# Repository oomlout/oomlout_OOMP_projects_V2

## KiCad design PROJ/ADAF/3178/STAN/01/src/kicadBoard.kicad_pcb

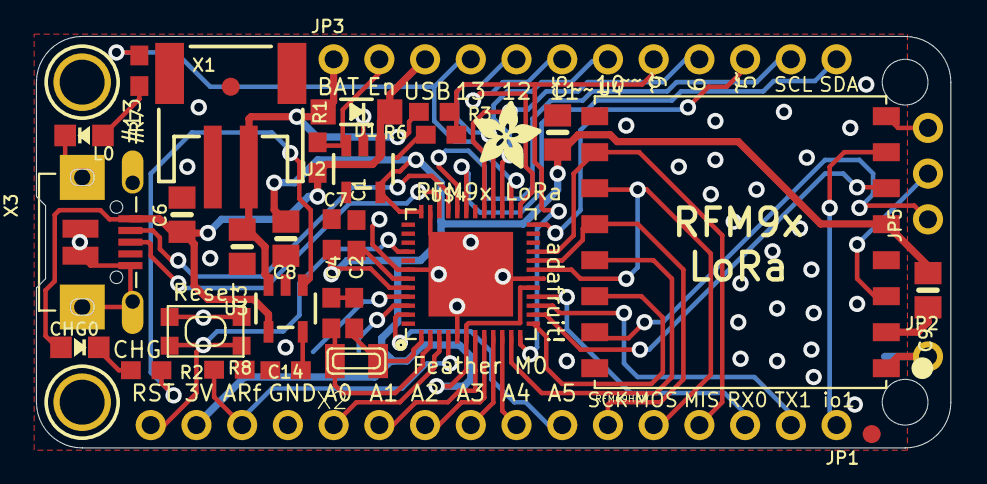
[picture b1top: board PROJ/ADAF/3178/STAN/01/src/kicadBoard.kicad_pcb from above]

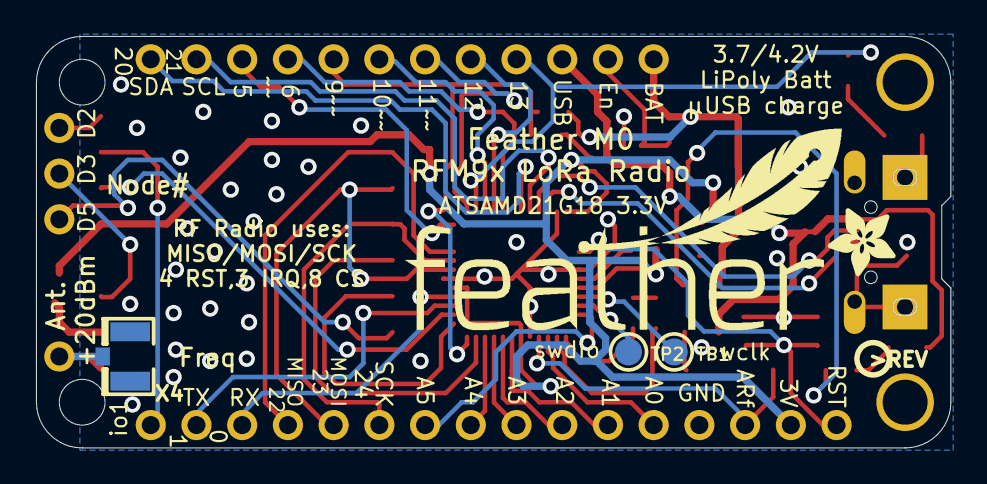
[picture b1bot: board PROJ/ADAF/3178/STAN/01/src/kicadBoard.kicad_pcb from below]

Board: 2 copper layers, 50.8 x 22.9 mm, 44 parts (6 on the bottom side), 46 nets.

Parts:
@HOLE0, @HOLE1: (no value)
C1, C7, C14: 1uF; 0603-NO
C2, C4: 22pF; 0603-NO
C3, C6, C8: 10µF; 0805-NO
C5, C9: 10uF; 0805-NO
CHG0: ORANGE; CHIPLED_0805_NOOUTLINE
D1: MBR120; SOD-123
JP1: 1X16_ROUND
JP2: 1X01_ROUND
JP3: 1X12_ROUND
JP5: 1X03_ROUND
L0: RED; CHIPLED_0805_NOOUTLINE
R1, R3: 100k; 0603-NO
R2: 1K; 0603-NO
R6: 100K; 0603-NO
R7: 2.2K; 0603-NO
R8: 10K\; 0603-NO
SW1: SPST_TACT-KMR2; KMR2
TP1, TP2: TESTPOINT_ROUND_1.5MM
U2: AP2112K-3.3; SOT23-5
U3: MCP73831T-2ACI/OT; SOT23-5
U4: RFM69HCW; RFMHCW_SMT
U$4: ATSAMD21G18_QFN; TQFN48_7MM
U$7, U$12: ADAFRUIT_3.5MM
U$9: FEATHERLOGO
U$13: PCBFEAT-REV-040
U$31, U$32: MOUNTINGHOLE2.5; MOUNTINGHOLE_2.5_PLATED
U$34, U$35: FIDUCIAL""; FIDUCIAL_1MM
X1: JSTPH; JSTPH2
X2: 32.768; XTAL3215
X3: microUSB; 4UCONN_20329_V2
X4: uFL; U.FL

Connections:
+3V3: C5.1, C7.1, C8.1, C9.1, JP1.15, U2.5, U4.5P, U$4.6, U$4.17, U$4.36, U$4.44
A0: JP1.12, U$4.3
A1: JP1.11, U$4.7
A2: JP1.10, U$4.8
A3: JP1.9, U$4.9
A4: JP1.8, U$4.10
A5: JP1.7, U$4.47
ANT: JP2.1, U4.1P, X4.3
AREF: C14.1, JP1.14, U$4.4
D0: JP1.3, U$4.16
D1: JP1.2, U$4.15
D3_IRQ: U4.6P, U$4.14
D4_RST: U4.14P, U$4.13
D5: JP3.10, U$4.24
D6: JP3.9, U$4.29
D8_CS: U4.13P, U$4.11
D9: JP3.8, R3.2, R6.1, U$4.12
D10: JP3.7, U$4.27
D11: JP3.6, U$4.25
D12: JP3.5, U$4.28
D13: JP3.4, R7.1, U$4.26
D+: U$4.34, X3.D+
D-: U$4.33, X3.D-
DIO1: JP1.1, U4.7P
DIO2: JP5.3, U4.8P
DIO3: JP5.2, U4.3P
DIO5: JP5.1, U4.15P
EN: JP3.2, R1.2, U2.3
GND: C1.2, C2.2, C3.2, C4.2, C5.2, C6.2, C7.2, C8.2, C9.2, C14.2, JP1.13, L0.C, R6.2, R8.2, SW1.2, SW1.4, U2.2, U3.2, U4.2P, U4.9P, U4.16P, U$4.5, U$4.18, U$4.35, U$4.42, U$4.THERMAL, X1.1, X3.BASE@1, X3.BASE@2, X3.GND, X3.SPRT@1, X3.SPRT@2, X3.SPRT@3, X3.SPRT@4, X4.1, X4.2
MISO: JP1.4, U4.10P, U$4.21
MOSI: JP1.5, U4.11P, U$4.19
unnamed: CHG0.C, R2.1
unnamed: L0.A, R7.2
unnamed: R2.2, U3.1
unnamed: R8.1, U3.5
unnamed: C2.1, U$4.1, X2.P$1
unnamed: C4.1, U$4.2, X2.P$2
SCK: JP1.6, U4.12P, U$4.20
SCL: JP3.11, U$4.32
SDA: JP3.12, U$4.31
SWCLK: TP1.P$1, U$4.45
SWDIO: TP2.P$1, U$4.46
VBAT: C3.1, D1.A, JP3.1, R3.1, U3.3, X1.2
VBUS: C6.1, CHG0.A, D1.C, JP3.3, R1.1, U2.1, U3.4, X3.VBUS
VDDCORE: C1.1, U$4.43
~RESET: JP1.16, SW1.1, SW1.3, U$4.40

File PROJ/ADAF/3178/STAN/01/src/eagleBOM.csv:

"Part";"Value";"Device";"Package";"Description";"BOM";
"C1";"1uF";"CAP_CERAMIC0603_NO";"0603-NO";"Ceramic Capacitors";"";
"C2";"22pF";"CAP_CERAMIC0603_NO";"0603-NO";"Ceramic Capacitors";"";
"C3";"10µF";"CAP_CERAMIC0805-NOOUTLINE";"0805-NO";"Ceramic Capacitors";"";
"C4";"22pF";"CAP_CERAMIC0603_NO";"0603-NO";"Ceramic Capacitors";"";
"C5";"10uF";"CAP_CERAMIC0805-NOOUTLINE";"0805-NO";"Ceramic Capacitors";"";
"C6";"10µF";"CAP_CERAMIC0805-NOOUTLINE";"0805-NO";"Ceramic Capacitors";"";
"C7";"1uF";"CAP_CERAMIC0603_NO";"0603-NO";"Ceramic Capacitors";"";
"C8";"10µF";"CAP_CERAMIC0805-NOOUTLINE";"0805-NO";"Ceramic Capacitors";"";
"C9";"10uF";"CAP_CERAMIC0805-NOOUTLINE";"0805-NO";"Ceramic Capacitors";"";
"C14";"1uF";"CAP_CERAMIC0603_NO";"0603-NO";"Ceramic Capacitors";"";
"CHG";"ORANGE";"LED0805_NOOUTLINE";"CHIPLED_0805_NOOUTLINE";"LED";"";
"D1";"MBR120";"DIODE-SCHOTTKYSOD-123";"SOD-123";"";"";
"JP1";"";"HEADER-1X16ROUND";"1X16_ROUND";"PIN HEADER";"";
"JP2";"";"HEADER-1X1ROUND";"1X01_ROUND";"PIN HEADER";"";
"JP3";"";"HEADER-1X12";"1X12_ROUND";"";"";
"JP5";"";"HEADER-1X3ROUND";"1X03_ROUND";"PIN HEADER";"";
"L";"RED";"LED0805_NOOUTLINE";"CHIPLED_0805_NOOUTLINE";"LED";"";
"R1";"100k";"RESISTOR_0603_NOOUT";"0603-NO";"Resistors";"";
"R2";"1K";"RESISTOR_0603_NOOUT";"0603-NO";"Resistors";"";
"R3";"100k";"RESISTOR_0603_NOOUT";"0603-NO";"Resistors";"";
"R6";"100K";"RESISTOR_0603_NOOUT";"0603-NO";"Resistors";"";
"R7";"2.2K";"RESISTOR_0603_NOOUT";"0603-NO";"Resistors";"";
"R8";"10K\";"RESISTOR_0603_NOOUT";"0603-NO";"Resistors";"";
"SW1";"SPST_TACT-KMR2";"SPST_TACT-KMR2";"KMR2";"SMT 6mm switch, EVQQ2 series";"";
"TP1";"";"TESTPOINTROUND1.5MM";"TESTPOINT_ROUND_1.5MM";"Test Point";"";
"TP2";"";"TESTPOINTROUND1.5MM";"TESTPOINT_ROUND_1.5MM";"Test Point";"";
"U$4";"ATSAMD21G18_QFN";"ATSAMD21J_QFN";"TQFN48_7MM";"";"";
"U$31";"MOUNTINGHOLE2.5";"MOUNTINGHOLE2.5";"MOUNTINGHOLE_2.5_PLATED";"Mounting Hole";"EXCLUDE";
"U$32";"MOUNTINGHOLE2.5";"MOUNTINGHOLE2.5";"MOUNTINGHOLE_2.5_PLATED";"Mounting Hole";"EXCLUDE";
"U$34";"FIDUCIAL""";"FIDUCIAL""";"FIDUCIAL_1MM";"Fiducial Alignment Points";"EXCLUDE";
"U$35";"FIDUCIAL""";"FIDUCIAL""";"FIDUCIAL_1MM";"Fiducial Alignment Points";"EXCLUDE";
"U2";"AP2112K-3.3";"VREG_SOT23-5";"SOT23-5";"SOT23-5 Fixed Voltage Regulators";"";
"U3";"MCP73831T-2ACI/OT";"MCP73831/2";"SOT23-5";"MCP73831/2 LIPO Charger";"";
"U4";"RFM69HCW";"RFM69HCW_SMT";"RFMHCW_SMT";"RFM69HCW - ISM Band RF Transceiver";"";
"X1";"JSTPH";"CON_JST_PH_2PIN";"JSTPH2";"JST 2-Pin Right-Angle Connector";"";
"X2";"32.768";"XTAL-3.2X1.5";"XTAL3215";"Low cost SMT crystals, no capacitors included";"";
"X3";"microUSB";"USB_MICRO_20329_V2";"4UCONN_20329_V2";"USB Connectors";"";
"X4";"uFL";"ANTENNA_U.FL";"U.FL";"U.FL Antenna Connector";"";

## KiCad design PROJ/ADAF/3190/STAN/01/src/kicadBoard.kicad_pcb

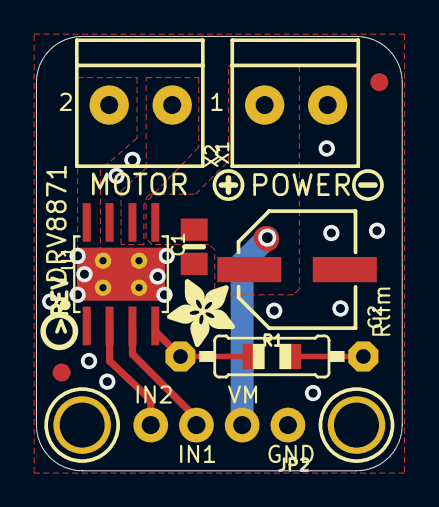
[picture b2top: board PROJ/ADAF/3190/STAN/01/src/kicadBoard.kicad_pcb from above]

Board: 2 copper layers, 20.3 x 24.1 mm, 15 parts (0 on the bottom side), 7 nets.

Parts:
C1: 0.1uF/50V; 0805-NO
C2: 22uF/63V; PANASONIC_D
FID1, FID2: FIDUCIAL""; FIDUCIAL_1MM
JP2: 1X04_ROUND_76
R1: 30K; 0805-THM
U1: DRV8871; HSOP8
U$9, U$10: MOUNTINGHOLE2.5; MOUNTINGHOLE_2.5_PLATED
U$11: SYMBOL_PLUS
U$12: SYMBOL_MINUS
U$14: ADAFRUIT_3.5MM
U$15: PCBFEAT-REV-040
X1: DCMOTOR; TERMBLOCK_1X2-3.5MM
X2: POWER; TERMBLOCK_1X2-3.5MM

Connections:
GND: C1.2, C2.-, JP2.1, R1.1, U1.1, U1.7, U1.GND, U1.P$1, U1.P$2, U1.P$3, U1.P$4, X2.2
IN1: JP2.3, U1.3
IN2: JP2.4, U1.2
unnamed: R1.2, U1.4
OUT1: U1.6, X1.2
OUT2: U1.8, X1.1
VMOTOR: C1.1, C2.+, JP2.2, U1.5, X2.1

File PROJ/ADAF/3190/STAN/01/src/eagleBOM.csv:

"Part";"Value";"Device";"Package";"Description";"BOM";
"C1";"0.1uF/50V";"CAP_CERAMIC0805-NOOUTLINE";"0805-NO";"Ceramic Capacitors";"";
"C2";"22uF/63V";"CAP_ELECTROLYTICPANASONIC_D";"PANASONIC_D";"Electrolytic Capacitors";"";
"FID1";"FIDUCIAL""";"FIDUCIAL""";"FIDUCIAL_1MM";"Fiducial Alignment Points";"EXCLUDE";
"FID2";"FIDUCIAL""";"FIDUCIAL""";"FIDUCIAL_1MM";"Fiducial Alignment Points";"EXCLUDE";
"JP2";"";"HEADER-1X476MIL";"1X04_ROUND_76";"PIN HEADER";"";
"R1";"30K";"FLIPFLOP-RES";"0805-THM";"Flip Flop resistor";"";
"U$9";"MOUNTINGHOLE2.5";"MOUNTINGHOLE2.5";"MOUNTINGHOLE_2.5_PLATED";"Mounting Hole";"EXCLUDE";
"U$10";"MOUNTINGHOLE2.5";"MOUNTINGHOLE2.5";"MOUNTINGHOLE_2.5_PLATED";"Mounting Hole";"EXCLUDE";
"U1";"DRV8871";"DRV8871";"HSOP8";"DRV8871 - 3.6A PWM Motor Driver";"";
"X1";"DCMOTOR";"TERMBLOCK_1X2";"TERMBLOCK_1X2-3.5MM";"3.5mm Terminal block";"";
"X2";"POWER";"TERMBLOCK_1X2";"TERMBLOCK_1X2-3.5MM";"3.5mm Terminal block";"";

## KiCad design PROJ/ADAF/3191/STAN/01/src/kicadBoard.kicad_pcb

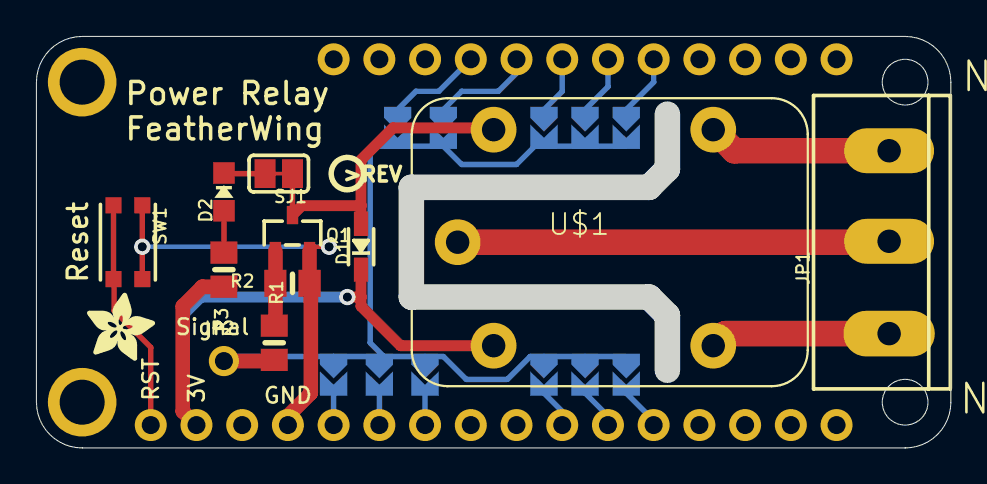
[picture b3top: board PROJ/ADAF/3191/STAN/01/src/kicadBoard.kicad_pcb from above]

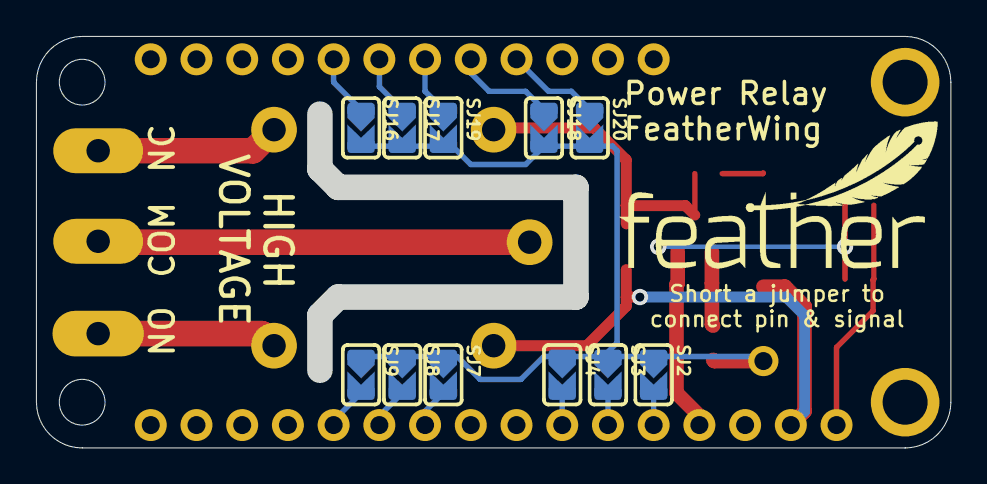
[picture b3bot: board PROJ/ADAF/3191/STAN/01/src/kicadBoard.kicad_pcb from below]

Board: 2 copper layers, 50.8 x 22.9 mm, 26 parts (12 on the bottom side), 22 nets.

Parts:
D1: 1N4148; SOD-323
D2: RED; CHIPLED_0805_NOOUTLINE
JP1: TERMBLOCK_1X3_5.08MM
JP2: 1X01_ROUND
MS2: FEATHERWING
Q1: MMBT2222; SOT23-R
R1, R3: 1K; 0805-NO
R2: 10K; 0805-NO
SJ1: SOLDERJUMPER_CLOSEDWIRE
SJ2, SJ3, SJ4, SJ7, SJ8, SJ9, SJ16, SJ17, SJ18, SJ19, SJ20: SOLDERJUMPER_ARROW_NOPASTE
SW1: KMR2; BTN_KMR2_4.6X2.8
U$1: RELAY_G5LE; RELAY_G5LE-1
U$5: PCBFEAT-REV-040
U$6: ADAFRUIT_3.5MM
U$7: FEATHERLOGO_MED

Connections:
3.3V: D1.C, MS2.2, R3.2, U$1.2
GND: MS2.4, Q1.2, R2.1, SW1.A, SW1.A'
unnamed: JP1.2, U$1.1
unnamed: JP1.3, U$1.3
unnamed: JP1.1, U$1.4
unnamed: D1.A, Q1.3, SJ1.1, U$1.5
unnamed: MS2.12, SJ9.2
unnamed: MS2.11, SJ8.2
unnamed: MS2.10, SJ7.2
unnamed: MS2.7, SJ4.2
unnamed: MS2.6, SJ3.2
unnamed: MS2.5, SJ2.2
unnamed: MS2.25, SJ20.1
unnamed: MS2.24, SJ18.1
unnamed: MS2.1, SW1.B, SW1.B'
unnamed: MS2.23, SJ19.1
unnamed: MS2.22, SJ17.1
unnamed: MS2.21, SJ16.1
unnamed: Q1.1, R1.2, R2.2
unnamed: D2.C, SJ1.2
unnamed: D2.A, R3.1
RELAYSIGNAL: JP2.1, R1.1, SJ2.1, SJ3.1, SJ4.1, SJ7.1, SJ8.1, SJ9.1, SJ16.2, SJ17.2, SJ18.2, SJ19.2, SJ20.2

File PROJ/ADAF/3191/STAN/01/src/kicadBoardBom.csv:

"Id";"Designator";"Package";"Quantity";"Designation";"Supplier and ref";
1;"Q1";"SOT23-R";1;"MMBT2222";;;
2;"R1,R3";"0805-NO";2;"1K";;;
3;"D1";"SOD-323";1;"1N4148";;;
4;"U$6";"ADAFRUIT_3.5MM";1;"";;;
5;"MS2";"FEATHERWING";1;"FEATHERWING";;;
6;"U$5";"PCBFEAT-REV-040";1;"";;;
7;"JP1";"TERMBLOCK_1X3_5.08MM";1;"";;;
8;"U$1";"RELAY_G5LE-1";1;"RELAY_G5LE";;;
9;"R2";"0805-NO";1;"10K";;;
10;"D2";"CHIPLED_0805_NOOUTLINE";1;"RED";;;
11;"SJ1";"SOLDERJUMPER_CLOSEDWIRE";1;"";;;
12;"SW1";"BTN_KMR2_4.6X2.8";1;"KMR2";;;
13;"JP2";"1X01_ROUND";1;"";;;
14;"U$7";"FEATHERLOGO_MED";1;"";;;
15;"SJ20,SJ8,SJ9,SJ4,SJ18,SJ17,SJ2,SJ3,SJ16,SJ19,SJ7";"SOLDERJUMPER_ARROW_NOPASTE";11;"";;;

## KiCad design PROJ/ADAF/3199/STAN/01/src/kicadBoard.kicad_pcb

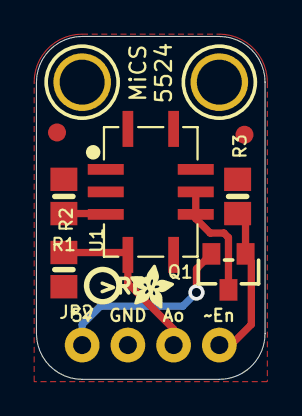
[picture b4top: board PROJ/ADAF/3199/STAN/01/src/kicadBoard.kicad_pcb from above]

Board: 2 copper layers, 12.7 x 19.0 mm, 12 parts (0 on the bottom side), 6 nets.

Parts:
FID1, FID2: FIDUCIAL""; FIDUCIAL_1MM
JP2: 1X04_ROUND_76
Q1: DMG3415U; SOT23-WIDE
R1: 82Ω 1%; 0805-NO
R2, R3: 10K; 0805-NO
U1: MiCS-5524; MICS-5524
U$3, U$4: MOUNTINGHOLE2.5; MOUNTINGHOLE_2.5_PLATED
U$7: ADAFRUIT_2.5MM
U$10: PCBFEAT-REV-040

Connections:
5.0V: JP2.1, Q1.2
AOUT: JP2.3, R2.2, U1.D
ENABLE: JP2.4, Q1.1, R3.1
GND: JP2.2, R1.1, R2.1, R3.2
HEATER: R1.2, U1.C
unnamed: Q1.3, U1.F, U1.G

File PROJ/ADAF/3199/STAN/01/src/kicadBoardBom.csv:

"Id";"Designator";"Package";"Quantity";"Designation";"Supplier and ref";
1;"U$4,U$3";"MOUNTINGHOLE_2.5_PLATED";2;"MOUNTINGHOLE2.5";;;
2;"U$7";"ADAFRUIT_2.5MM";1;"";;;
3;"JP2";"1X04_ROUND_76";1;"";;;
4;"R1";"0805-NO";1;"82Ω 1%";;;
5;"FID2,FID1";"FIDUCIAL_1MM";2;"FIDUCIAL""";;;
6;"Q1";"SOT23-WIDE";1;"DMG3415U";;;
7;"R2,R3";"0805-NO";2;"10K";;;
8;"U1";"MICS-5524";1;"MiCS-5524";;;
9;"U$10";"PCBFEAT-REV-040";1;"";;;

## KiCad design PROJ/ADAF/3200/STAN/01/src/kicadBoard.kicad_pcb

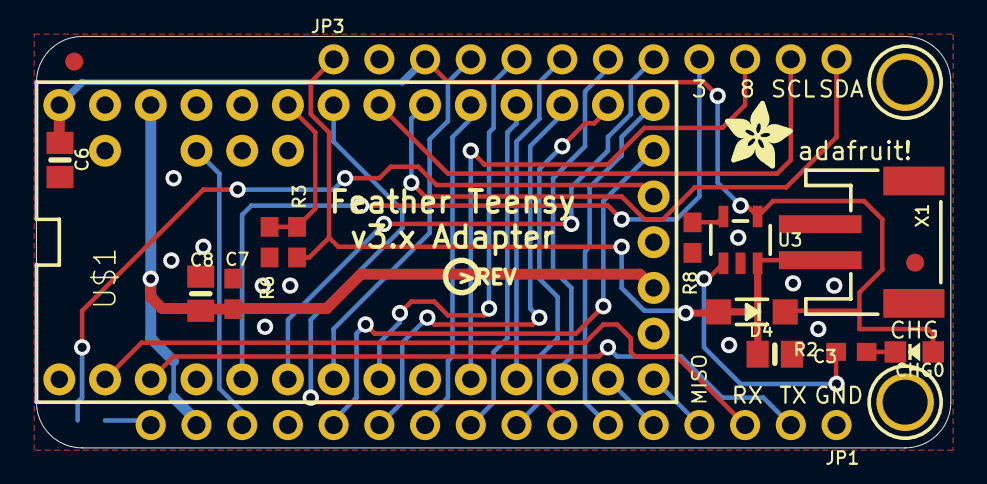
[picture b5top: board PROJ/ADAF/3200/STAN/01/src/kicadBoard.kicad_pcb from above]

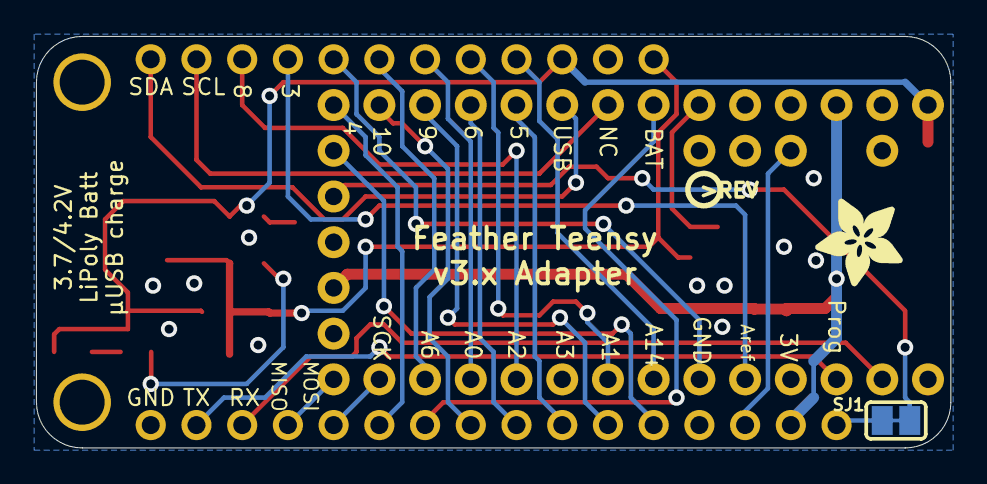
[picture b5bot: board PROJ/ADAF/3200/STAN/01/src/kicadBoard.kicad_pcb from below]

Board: 2 copper layers, 50.8 x 22.9 mm, 24 parts (3 on the bottom side), 31 nets.

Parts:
C3, C6, C8: 10µF; 0805-NO
C7: 1uF; 0603-NO
CHG0: ORANGE; CHIPLED_0805_NOOUTLINE
D4: MBR120; SOD-123
JP1: 1X16_ROUND
JP3: 1X12_ROUND
R2: 1K; 0603-NO
R3: 100k; 0603-NO
R6: 100K; 0603-NO
R8: 2.2K; 0603-NO
SJ1: SOLDERJUMPER_CLOSEDWIRE
U3: MCP73831T-2ACI/OT; SOT23-5
U$1: TEENSY_3.1_ALL_PINS; TEENSY3-ALL_PINS
U$4: ADAFRUIT_5MM
U$5, U$6: PCBFEAT-REV-040
U$7: ADAFRUIT_3.5MM
U$31, U$32: MOUNTINGHOLE2.5; MOUNTINGHOLE_2.5_PLATED
U$34, U$35: FIDUCIAL""; FIDUCIAL_1MM
X1: JSTPH; JSTPH2

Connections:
3: JP3.9, U$1.3
4: JP3.8, U$1.4
5: JP3.4, U$1.5
6: JP3.5, U$1.6
8: JP3.10, U$1.8
9: JP3.6, U$1.9
10: JP3.7, U$1.10
+3V3: C7.1, C8.1, JP1.15, U$1.3.3V, U$1.3.3V1
A0: JP1.8, U$1.14/A0
A1: JP1.11, U$1.15/A1
A2: JP1.9, U$1.16/A2
A3: JP1.10, U$1.17/A3
A6: JP1.7, U$1.20/A6
A7: R3.2, R6.1, U$1.21/A7
A14: JP1.12, U$1.RESET/DAC
AREF: JP1.14, U$1.AREF
BOOT: SJ1.2, U$1.PGM
GND: C3.2, C6.2, C7.2, C8.2, JP1.1, JP1.13, R6.2, R8.2, U3.2, U$1.GND, U$1.GND1, X1.1
MISO: JP1.4, U$1.12
MOSI: JP1.5, U$1.11
unnamed: CHG0.C, R2.1
unnamed: R2.2, U3.1
unnamed: R8.1, U3.5
RST/BOOT: JP1.16, SJ1.1
RX: JP1.3, U$1.0
SCK: JP1.6, U$1.13
SCL: JP3.11, U$1.19/A5
SDA: JP3.12, U$1.18/A4
TX: JP1.2, U$1.1
VBAT: C3.1, D4.A, JP3.1, R3.1, U3.3, X1.2
VBUS: C6.1, CHG0.A, D4.C, JP3.3, U3.4, U$1.VIN

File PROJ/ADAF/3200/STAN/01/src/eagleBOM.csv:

"Part";"Value";"Device";"Package";"Description";"BOM";
"C3";"10µF";"CAP_CERAMIC0805-NOOUTLINE";"0805-NO";"Ceramic Capacitors";"";
"C6";"10µF";"CAP_CERAMIC0805-NOOUTLINE";"0805-NO";"Ceramic Capacitors";"";
"C7";"1uF";"CAP_CERAMIC0603_NO";"0603-NO";"Ceramic Capacitors";"";
"C8";"10µF";"CAP_CERAMIC0805-NOOUTLINE";"0805-NO";"Ceramic Capacitors";"";
"CHG";"ORANGE";"LED0805_NOOUTLINE";"CHIPLED_0805_NOOUTLINE";"LED";"";
"D4";"MBR120";"DIODE-SCHOTTKYSOD-123";"SOD-123";"";"";
"JP1";"";"HEADER-1X16ROUND";"1X16_ROUND";"PIN HEADER";"";
"JP3";"";"HEADER-1X12";"1X12_ROUND";"";"";
"R2";"1K";"RESISTOR_0603_NOOUT";"0603-NO";"Resistors";"";
"R3";"100k";"RESISTOR_0603_NOOUT";"0603-NO";"Resistors";"";
"R6";"100K";"RESISTOR_0603_NOOUT";"0603-NO";"Resistors";"";
"R8";"2.2K";"RESISTOR_0603_NOOUT";"0603-NO";"Resistors";"";
"SJ1";"";"SOLDERJUMPERCLOSED";"SOLDERJUMPER_CLOSEDWIRE";"SMD Solder JUMPER";"";
"U$1";"TEENSY_3.1_ALL_PINS";"TEENSY_3.1_ALL_PINS";"TEENSY3-ALL_PINS";"Footprint for Teensy 3.1 or 3.2 board using all through-holes, i.e. the entire perimeter plus the 4 through-holes inboard (A10,A11,AREF, VUSB)";"";
"U$31";"MOUNTINGHOLE2.5";"MOUNTINGHOLE2.5";"MOUNTINGHOLE_2.5_PLATED";"Mounting Hole";"EXCLUDE";
"U$32";"MOUNTINGHOLE2.5";"MOUNTINGHOLE2.5";"MOUNTINGHOLE_2.5_PLATED";"Mounting Hole";"EXCLUDE";
"U$34";"FIDUCIAL""";"FIDUCIAL""";"FIDUCIAL_1MM";"Fiducial Alignment Points";"EXCLUDE";
"U$35";"FIDUCIAL""";"FIDUCIAL""";"FIDUCIAL_1MM";"Fiducial Alignment Points";"EXCLUDE";
"U3";"MCP73831T-2ACI/OT";"MCP73831/2";"SOT23-5";"MCP73831/2 LIPO Charger";"";
"X1";"JSTPH";"CON_JST_PH_2PIN";"JSTPH2";"JST 2-Pin Right-Angle Connector";"";

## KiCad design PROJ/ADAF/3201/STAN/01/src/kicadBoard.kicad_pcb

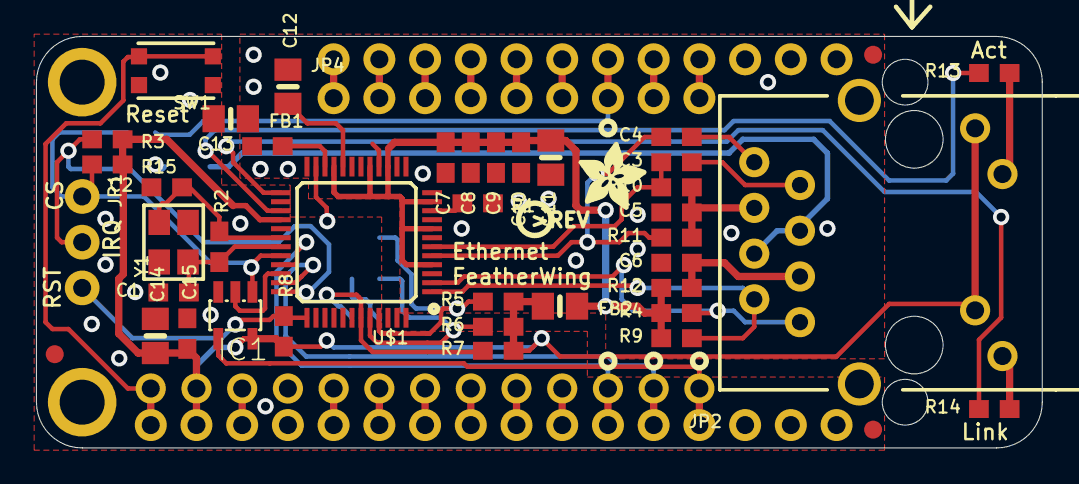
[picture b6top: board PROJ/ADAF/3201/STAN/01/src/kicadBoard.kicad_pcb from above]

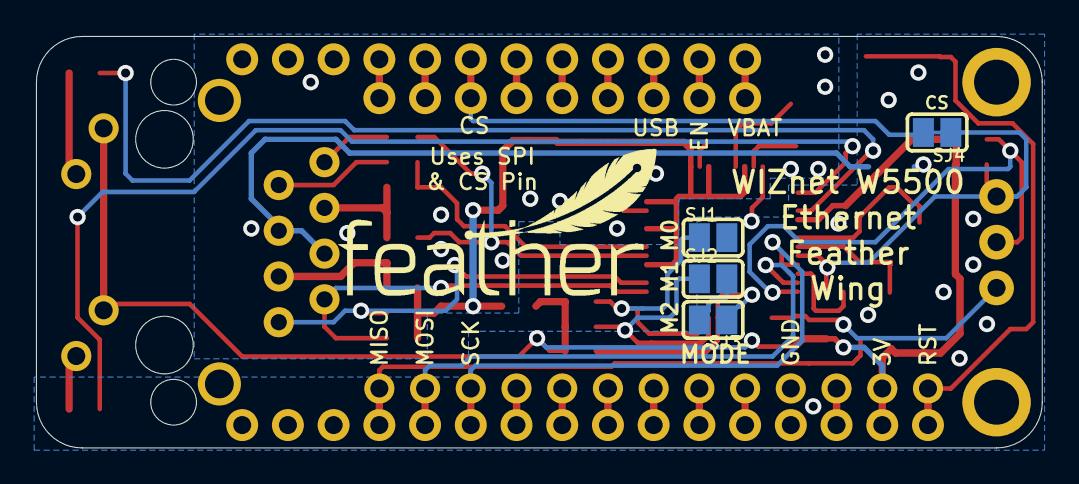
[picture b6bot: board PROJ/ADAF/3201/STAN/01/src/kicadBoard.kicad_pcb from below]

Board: 2 copper layers, 55.9 x 22.9 mm, 51 parts (5 on the bottom side), 48 nets.

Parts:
C1, C2: 22pF; 0603-NO
C3, C4: 6.8nF; 0603-NO
C5, C6: 10nF; 0603-NO
C7, C8, C9, C10, C13, C15: 0.1uF; 0603-NO
C11, C12, C14: 10uF; 0805-NO
FB1, FB2: ferrite; 0805-NO
FID1, FID2, FID3: FIDUCIAL""; FIDUCIAL_1MM
IC1: 74AHC1G125; SOT23-5L
JP1: 1X03_ROUND_76
JP2: 1X13_ROUND_70
JP4: 1X09_ROUND_70
MS1: FEATHERWING_NODIM
R1: 12.4K; 0603-NO
R2: 1M; 0603-NO
R3, R5, R6, R7, R8, R15: 10K; 0603-NO
R4, R9, R10, R11: 49.9; 0603-NO
R12: 10; 0603-NO
R13, R14: 470; 0603-NO
SJ1, SJ2, SJ3: SOLDERJUMPER_REFLOW_NOPASTE
SJ4: SOLDERJUMPER_CLOSEDWIRE
SW1: KMR2; BTN_KMR2_4.6X2.8
U$1: W5500; LQFP48
U$45: PCBFEAT-REV-040
U$48: FEATHERLOGO_MED
U$49: ADAFRUIT_3.5MM
X1: RB1-125BAG1A; RJ45_PULSEJACK
Y1: 25MHz; CRYSTAL_3.2X2.5

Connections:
3.3V: C14.1, C15.1, FB2.1, IC1.5, JP2.12, MS1.2, R3.2, R5.1, R6.1, R7.1, R8.1, R15.2, U$1.28, X1.10, X1.12
AGND: C5.2, C6.2, C7.2, C8.2, C9.2, C10.2, C11.2, C12.2, C13.2, FB1.2, R1.2, U$1.3, U$1.9, U$1.14, U$1.16, U$1.19, U$1.48
AVDD: C7.1, C8.1, C9.1, C10.1, C11.1, FB2.2, R4.2, R9.2, R12.2, U$1.4, U$1.8, U$1.11, U$1.15, U$1.17, U$1.21
CS: IC1.1, JP1.1, R15.1, SJ4.1, U$1.32
GND: C1.2, C2.2, C14.2, C15.2, FB1.1, IC1.3, JP2.10, MS1.4, SJ1.2, SJ2.2, SJ3.2, SW1.A, SW1.A', U$1.23, U$1.29, X1.4, X1.5
GREENLED: R14.1, X1.9
IRQ: JP1.2, R3.1, U$1.36
MISO: IC1.2, U$1.34
MISO_MCU: IC1.4, JP2.1, MS1.13
MOSI: JP2.2, MS1.12, U$1.35
unnamed: C1.1, R2.1, U$1.31, Y1.1
unnamed: C2.1, R2.2, U$1.30, Y1.2
unnamed: R1.1, U$1.10
unnamed: R5.2, SJ1.1, U$1.45
unnamed: R6.2, SJ2.1, U$1.44
unnamed: R7.2, SJ3.1, U$1.43
unnamed: C3.1, X1.7
unnamed: C4.1, X1.8
unnamed: C5.1, R10.1, R11.1, X1.6
unnamed: C6.1, R12.1, X1.3
unnamed: C13.1, U$1.22
unnamed: C12.1, U$1.20
unnamed: R13.2, U$1.27
unnamed: R14.2, U$1.25
unnamed: JP4.2, MS1.27
unnamed: JP4.4, MS1.25
unnamed: JP4.5, MS1.24
unnamed: JP4.6, MS1.23
unnamed: JP4.7, MS1.22, SJ4.2
unnamed: JP4.8, MS1.21
unnamed: JP4.9, MS1.20
unnamed: JP2.13, MS1.1, SW1.B, SW1.B'
unnamed: JP2.4, MS1.10
unnamed: JP2.5, MS1.9
unnamed: JP2.6, MS1.8
unnamed: JP2.7, MS1.7
unnamed: JP2.8, MS1.6
unnamed: JP2.9, MS1.5
unnamed: JP2.11, MS1.3
RESET: JP1.3, R8.2, U$1.37
RX+: C3.2, R10.2, U$1.6
RX-: C4.2, R11.2, U$1.5
SCK: JP2.3, MS1.11, U$1.33
TX+: R4.1, U$1.2, X1.1
TX-: R9.1, U$1.1, X1.2
USB: JP4.3, MS1.26
VBAT: JP4.1, MS1.28
YELLOWLED: R13.1, X1.11

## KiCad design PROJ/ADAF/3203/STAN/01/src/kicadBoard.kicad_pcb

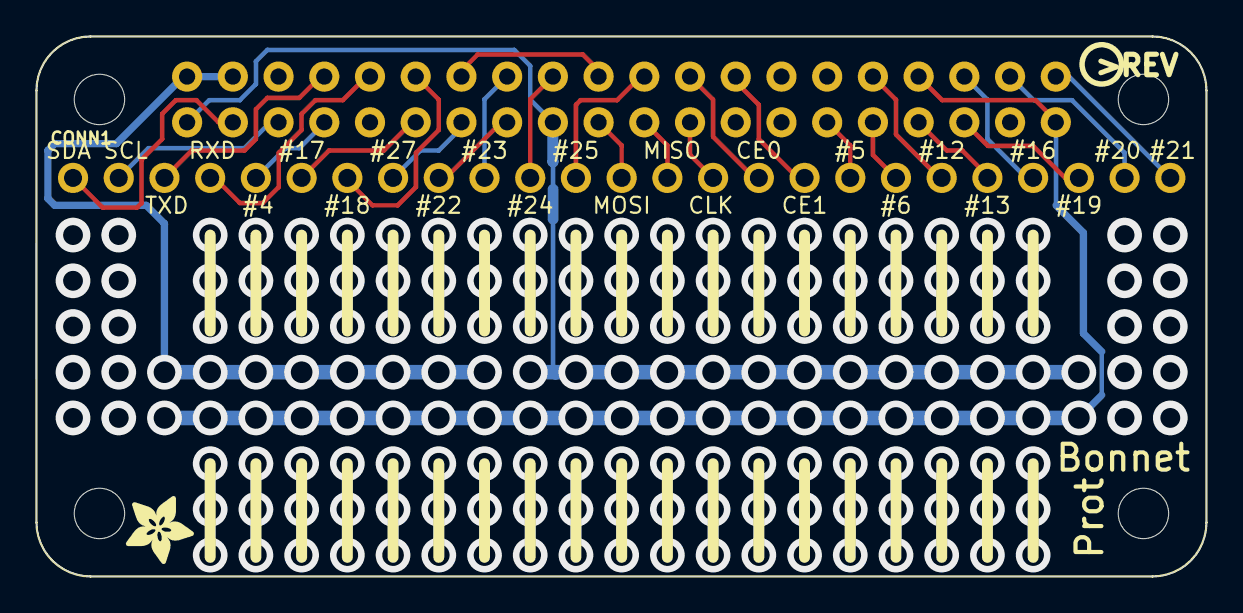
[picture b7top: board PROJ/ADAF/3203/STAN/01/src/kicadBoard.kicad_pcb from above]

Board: 2 copper layers, 65.0 x 30.0 mm, 4 parts (0 on the bottom side), 28 nets.

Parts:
CONN1: HEADER-1X25; 1X25_ROUND_70MIL
RPI1: RASPBERRYPI_BPLUS_BONNETNODIM; PI_BONNET_NODIM
U$1: ADAFRUIT_3.5MM
U$3: PCBFEAT-REV-056

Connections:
3.3V: RPI1.1, RPI1.17
5.0V: RPI1.2, RPI1.4
GND: RPI1.6, RPI1.9, RPI1.14, RPI1.20, RPI1.25, RPI1.30, RPI1.34, RPI1.39
GPIO4: CONN1.5, RPI1.7
GPIO5: CONN1.18, RPI1.29
GPIO6: CONN1.19, RPI1.31
GPIO12: CONN1.20, RPI1.32
GPIO13: CONN1.21, RPI1.33
GPIO16: CONN1.22, RPI1.36
GPIO17: CONN1.6, RPI1.11
GPIO18: CONN1.7, RPI1.12
GPIO19: CONN1.23, RPI1.35
GPIO20: CONN1.24, RPI1.38
GPIO21: CONN1.25, RPI1.40
GPIO22: CONN1.9, RPI1.15
GPIO23: CONN1.10, RPI1.16
GPIO24: CONN1.11, RPI1.18
GPIO25: CONN1.12, RPI1.22
GPIO27: CONN1.8, RPI1.13
RXD: CONN1.4, RPI1.10
SCL: CONN1.2, RPI1.5
SDA: CONN1.1, RPI1.3
SPI_CE0: CONN1.16, RPI1.24
SPI_CE1: CONN1.17, RPI1.26
SPI_MISO: CONN1.14, RPI1.21
SPI_MOSI: CONN1.13, RPI1.19
SPI_SCLK: CONN1.15, RPI1.23
TXD: CONN1.3, RPI1.8

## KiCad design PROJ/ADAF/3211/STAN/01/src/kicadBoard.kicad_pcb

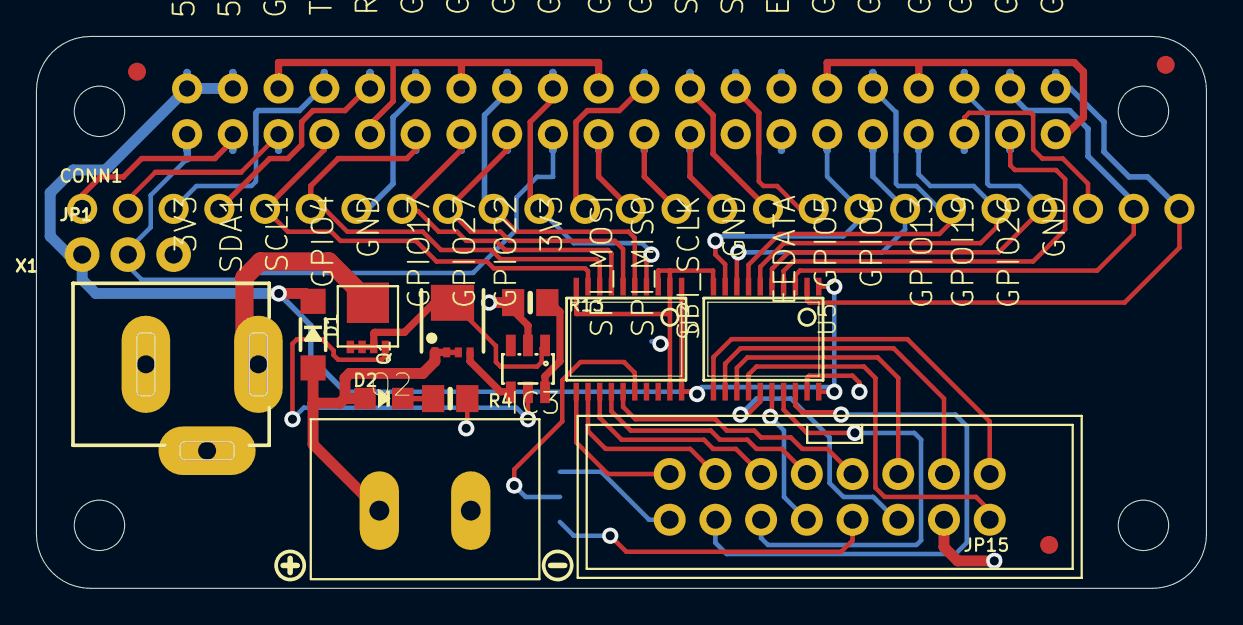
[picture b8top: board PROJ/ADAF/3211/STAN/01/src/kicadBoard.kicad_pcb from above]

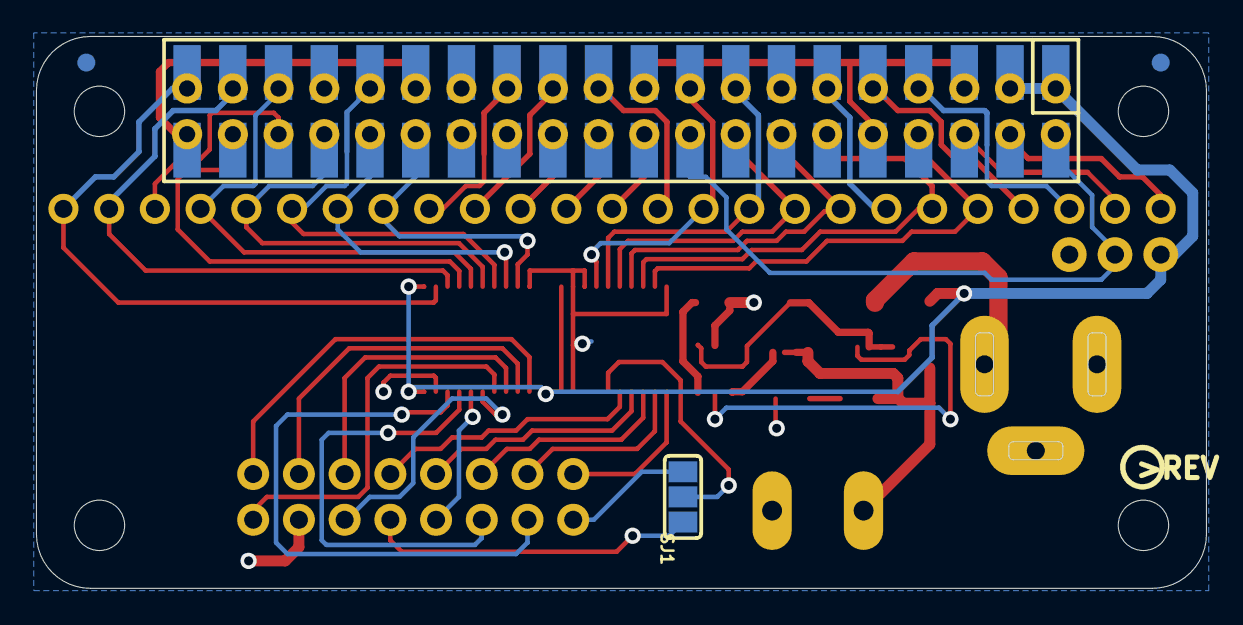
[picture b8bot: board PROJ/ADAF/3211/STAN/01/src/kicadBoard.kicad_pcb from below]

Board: 2 copper layers, 65.0 x 30.7 mm, 24 parts (3 on the bottom side), 54 nets.

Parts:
CONN1: HEADER-1X25; 1X25_ROUND_70MIL
D1: MBR120; SOD-123
D2: green; CHIPLED_0805_NOOUTLINE
FID1, FID2, FID3: FIDUCIAL_1MM
IC3: MAX4866T; SOT23-6
JP1: 1X03_ROUND_76
JP15: 2X08_SHROUDED
MATRIX_PWR0: PINHEAD; TERMBLOCK508
Q1: AON3414; POWERPAK-1212-8
Q2: AON7401; POWERDI3333
R4, R13: 1K; 0805-NO
RPI1: RASPBERRYPI_BPLUS_BONNET_THMSMT; PI_BONNET_THMSMT
SJ1: SOLDERJUMPER_2WAY_OPEN_NOPASTE
U3, U5: 74AHCT245; TSSOP20
U$1: BONNET_MATRIX_TOP
U$3: PCBFEAT-REV-056
U$6: BONNET_MATRIX_BOT
U$10: SYMBOL_PLUS
U$11: SYMBOL_MINUS
X1: 2.1mm DC; DCJACK_2MM_PTH

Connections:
3.3V: JP1.2, RPI1.1, RPI1.17, RPI1.S1, RPI1.S17
5.0V: D1.A, D2.A, MATRIX_PWR0.P$4, Q1.1, Q1.2, Q1.3
5VIN: Q2.5678, X1.PWR
+5V: D1.C, JP1.1, RPI1.2, RPI1.4, RPI1.S2, RPI1.S4, U3.1, U3.20, U5.1, U5.20
CLK: JP15.13, U3.12
EECLK: RPI1.28, RPI1.S28
EEDATA: RPI1.27, RPI1.S27
GND: IC3.2, JP1.3, JP15.4, MATRIX_PWR0.P$3, R4.2, R13.1, RPI1.6, RPI1.9, RPI1.14, RPI1.20, RPI1.25, RPI1.30, RPI1.34, RPI1.39, RPI1.S6, RPI1.S9, RPI1.S14, RPI1.S20, RPI1.S25, RPI1.S30, RPI1.S34, RPI1.S39, U3.2, U3.3, U3.10, U3.19, U5.10, U5.19, X1.GND, X1.GNDBREAK
GPIO4: CONN1.5, RPI1.7, RPI1.S7, U3.9
GPIO5: CONN1.18, RPI1.29, RPI1.S29, U5.9
GPIO6: CONN1.19, RPI1.31, RPI1.S31, U5.8
GPIO12: CONN1.20, RPI1.32, RPI1.S32, U5.7
GPIO13: CONN1.21, RPI1.33, RPI1.S33, U5.6
GPIO16: CONN1.22, RPI1.36, RPI1.S36, U5.5
GPIO17: CONN1.6, RPI1.11, RPI1.S11, U3.8
GPIO18: CONN1.7, RPI1.12, RPI1.S12
GPIO19: CONN1.23, RPI1.35, RPI1.S35
GPIO20: CONN1.24, RPI1.38, RPI1.S38, U5.3
GPIO21: CONN1.25, RPI1.40, RPI1.S40, U5.2
GPIO22: CONN1.9, RPI1.15, RPI1.S15, U3.6
GPIO23: CONN1.10, RPI1.16, RPI1.S16, U3.5
GPIO24: CONN1.11, RPI1.18, RPI1.S18, U3.4
GPIO25: CONN1.12, RPI1.22, RPI1.S22
GPIO26: RPI1.37, RPI1.S37, U5.4
GPIO27: CONN1.8, RPI1.13, RPI1.S13, U3.7
LAT: JP15.14, U5.18
M1_A: JP15.9, U3.14
M1_B: JP15.10, U5.16
M1_B1: JP15.3, U5.12
M1_B2: JP15.7, U3.15
M1_C: JP15.11, U3.13
M1_D: JP15.12, U5.17
M1_E: SJ1.2, U3.16
M1_E': JP15.8, SJ1.1
M1_E'': JP15.16, SJ1.3
M1_G1: JP15.2, U5.14
M1_G2: JP15.6, U5.15
M1_R1: JP15.1, U5.11
M1_R2: JP15.5, U5.13
unnamed: IC3.6, R13.2
unnamed: D2.C, R4.1
unnamed: IC3.1, Q1.5-8, Q2.1, Q2.2, Q2.3
unnamed: IC3.4, Q1.4
unnamed: IC3.5, Q2.4
OE: JP15.15, U3.11
RXD: CONN1.4, RPI1.10, RPI1.S10
SCL: CONN1.2, RPI1.5, RPI1.S5
SDA: CONN1.1, RPI1.3, RPI1.S3
SPI_CE0: CONN1.16, RPI1.24, RPI1.S24
SPI_CE1: CONN1.17, RPI1.26, RPI1.S26
SPI_MISO: CONN1.14, RPI1.21, RPI1.S21
SPI_MOSI: CONN1.13, RPI1.19, RPI1.S19
SPI_SCLK: CONN1.15, RPI1.23, RPI1.S23
TXD: CONN1.3, RPI1.8, RPI1.S8
